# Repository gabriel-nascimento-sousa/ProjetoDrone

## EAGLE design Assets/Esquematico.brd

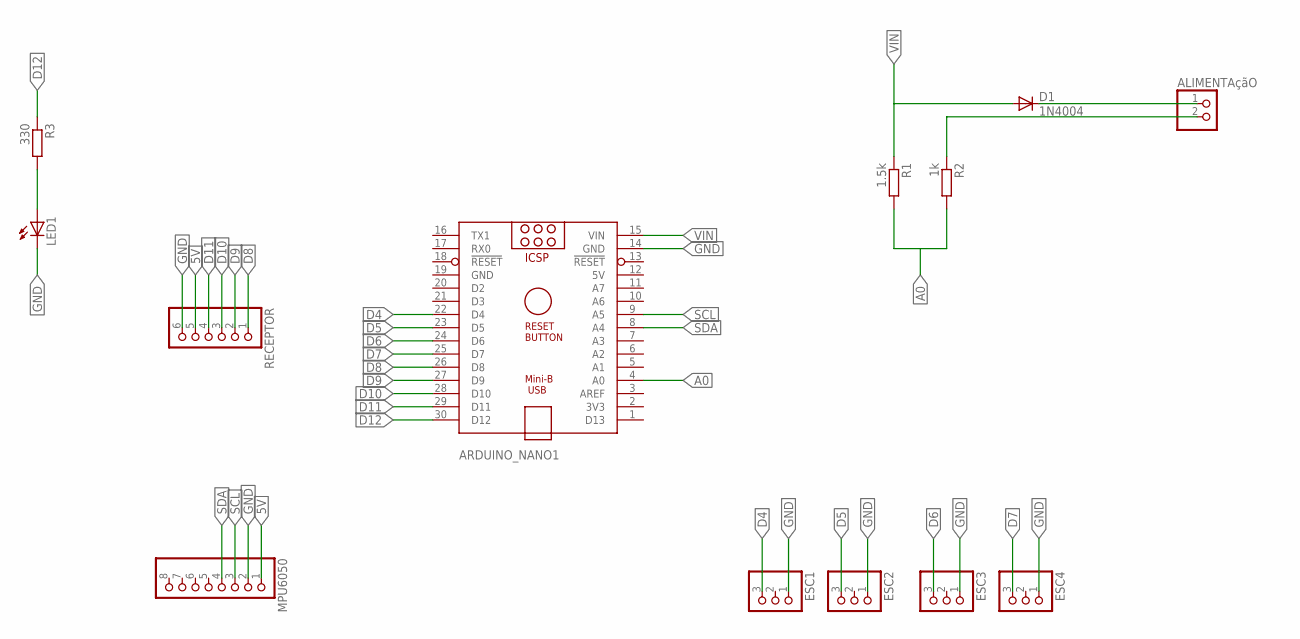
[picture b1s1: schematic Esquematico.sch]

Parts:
ALIMENTAçãO: PINHD-1X2; 1X02
ARDUINO_NANO1: ARDUINO_NANO
D1: 1N4004; DO41-10
ESC1, ESC2, ESC3, ESC4: PINHD-1X3; 1X03
LED1: LED3MM
MPU6050: PINHD-1X8; 1X08
R1: 1.5k; 0204/7
R2: 1k; 0204/7
R3: 330; 0204/7
RECEPTOR: PINHD-1X6; 1X06

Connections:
5V: ARDUINO_NANO1.12 (5V), MPU6050.1, RECEPTOR.5
A0: ARDUINO_NANO1.4 (A0), R1.2, R2.2
D4: ARDUINO_NANO1.22 (D4), ESC1.3
D5: ARDUINO_NANO1.23 (D5), ESC2.3
D6: ARDUINO_NANO1.24 (D6), ESC3.3
D7: ARDUINO_NANO1.25 (D7), ESC4.3
D8: ARDUINO_NANO1.26 (D8), RECEPTOR.1
D9: ARDUINO_NANO1.27 (D9), RECEPTOR.2
D10: ARDUINO_NANO1.28 (D10), RECEPTOR.3
D11: ARDUINO_NANO1.29 (D11), RECEPTOR.4
D12: ARDUINO_NANO1.30 (D12), R3.1
GND: ARDUINO_NANO1.14 (GND), ARDUINO_NANO1.19 (GND), ESC1.1, ESC2.1, ESC3.1, ESC4.1, LED1.K (C), MPU6050.2, RECEPTOR.6
unnamed: LED1.A, R3.2
unnamed: ALIMENTAçãO.1, D1.C
unnamed: ALIMENTAçãO.2, R2.1
SCL: ARDUINO_NANO1.9 (A5), MPU6050.3
SDA: ARDUINO_NANO1.8 (A4), MPU6050.4
VIN: ARDUINO_NANO1.15 (VIN), D1.A, R1.1

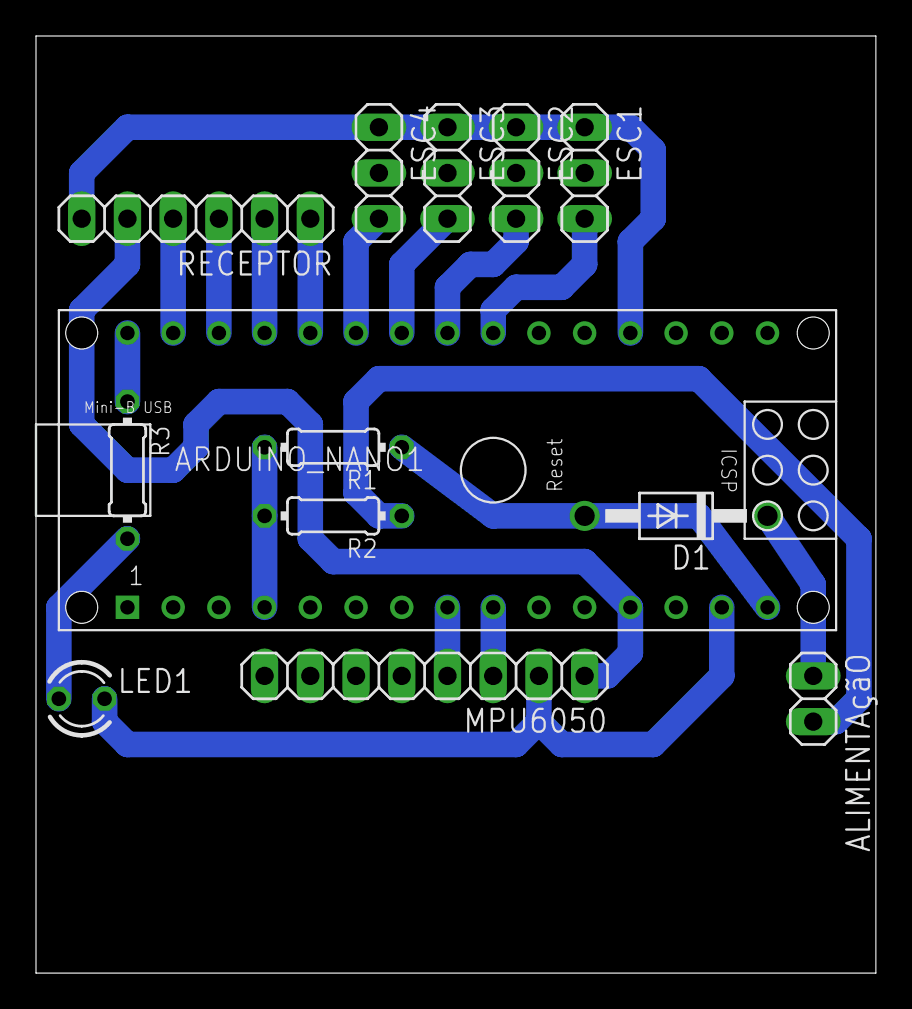
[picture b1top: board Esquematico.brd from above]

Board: 2 copper layers, 46.7 x 52.1 mm, 13 parts (0 on the bottom side), 18 nets.

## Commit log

2023-02-25 primeira commit
